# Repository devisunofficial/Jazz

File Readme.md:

# Jazz

Jazz is a bluetooth speaker that uses ESP32 for bluetooth connection

It focuses on minimalism and uses Audiophile grade equipments for good soundquality

### Features:

 - Compact design 
 - Capacitive Sensor to enter pairing mode
 - Toggle switch to On-Off speaker.
 - Daytone Speaker and Passive Radiator

### CAD Model:
It has 3 separate printed pieces. The Enclousure, the Speaker Holder to support driver and passive radiator, and Top mesh to cover driver.
Made in Autodesk Fusion.

### PCB:
Here's my PCB! It was made in KiCad. 

Schematic : 
PCB Footprint : 

### Firmware Overview:
Currently Firmware is underdevelopment so there is some time to finished product.
This speaker uses C++ firmware and Arduino IDE for Flashing.

### Assembly Instructions :
1. Flash Firmware in XIAO ESO32
2. Solder Pairing Switch, Kill Switch, Speaker, Battery
3. Test everything works
4. Apply Epoxy layer(not neccessary though but better if we do) inside shell to prevent air from leaking
5. Glue togetther the Speaker and Passive Radiater to Speaker holder (to prevent air from leaking) along with screws
6. Screw Speaker holder and Top Mesh to Encloudure.

### BOM Table
|Name|Use|Quantity|Distributer|
|-----|---|-------|-----------|
|Battery|Power Source|1|Robu|
|PCB|Main-Circuit|1|JLCPCB|
|Toggle switch|On-Off|1|Amazon|
|XIAO ESP32|Bluetooth SoC|1|Amazon|
|Speaker|Main Driver|1|Parts Express|
|Capacitive Touch Button|Pairing Mode|1|Amazon|
|AirTight Glue|Prevent Air Leaking|1|Amazon|

### Extra Stuff
I have provided an extra 3D printing Part in PR folder in CAD Folder because rather then paying $88 in shipping.
I didn't made that, and I don't have refinement in skills to make that. 
#### **CREDITS**  https://www.thingiverse.com/zx82net

Also I have added all screenshots of Cart in Screenshots_Cart Folder

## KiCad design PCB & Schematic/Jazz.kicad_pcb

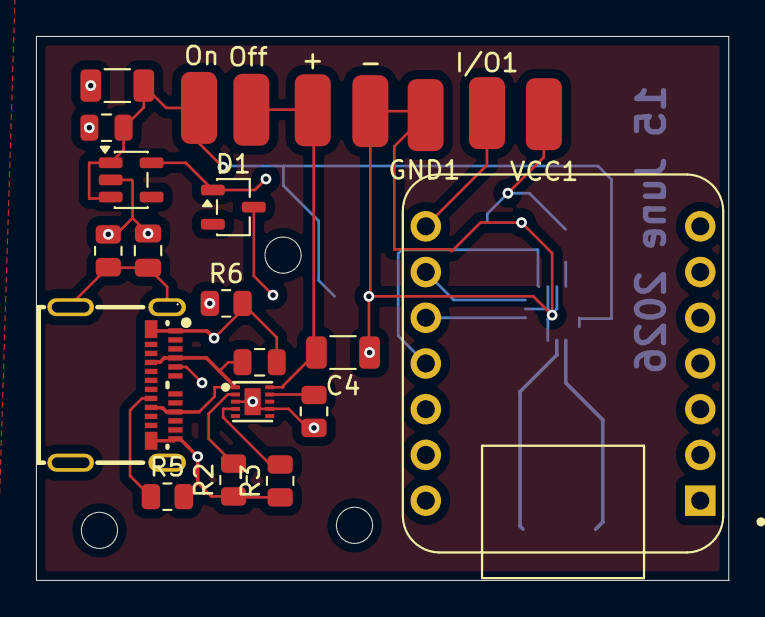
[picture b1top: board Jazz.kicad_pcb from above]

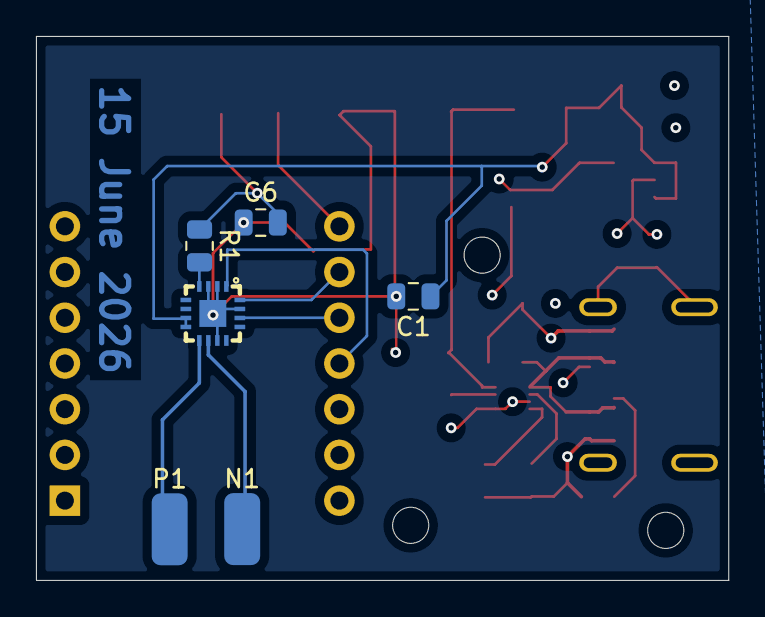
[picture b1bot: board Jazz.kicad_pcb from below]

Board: 4 copper layers, 38.5 x 30.2 mm, 29 parts (6 on the bottom side), 19 nets.

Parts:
+: MountingHole_Pad; SolderWirePad_1x01_SMD_2x4mm
-: MountingHole_Pad; SolderWirePad_1x01_SMD_2x4mm
C1: 0.1; C_0805_2012Metric
C2: 10; C_1206_3216Metric
C3, C5, C6: 1; C_0805_2012Metric
C4: 4.7; C_1206_3216Metric
C7: 4.7n; C_0805_2012Metric
D1: BAT54_C8590; SOT-23-3
GND1: MountingHole_Pad; SolderWirePad_1x01_SMD_2x4mm
I/O1: MountingHole_Pad; SolderWirePad_1x01_SMD_2x4mm
N1: MountingHole_Pad; SolderWirePad_1x01_SMD_2x4mm
Off: MountingHole_Pad; SolderWirePad_1x01_SMD_2x4mm
On: MountingHole_Pad; SolderWirePad_1x01_SMD_2x4mm
P1: MountingHole_Pad; SolderWirePad_1x01_SMD_2x4mm
R1: 560k; R_0805_2012Metric
R2: 1.1k; R_0805_2012Metric
R3: 2k; R_0805_2012Metric
R4: 10k; R_0805_2012Metric
R5, R6: 5.1k; R_0805_2012Metric
R7: 1M; R_0805_2012Metric
U1: XIAO-nRF52840-DIP; XIAO-Generic-Thruhole-14P-2.54-21X17.8MM
U2: TLV75533PDBVR; SOT-23-5
U3: BQ24040DSQT; WSON-10_L2.0-W2.0-P0.40-TL-EP
U4: MAX98357AETE+T; TQFN-16_L3.0-W3.0-P0.50-BL-EP1.5
USB-C-Port1: 105450-0101; USB-C-SMD_TYPE-C-USB-18
VCC1: MountingHole_Pad; SolderWirePad_1x01_SMD_2x4mm

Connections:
3.3V: C6.2, D1.1 (A), R1.1, U2.5 (OUT), VCC1.1
BCLK: U1.9 (P1.13_D8_SCK), U4.16 (BCLK)
Battery-Rail Out: +.1, C4.2, Off.1, U3.10 (OUT)
DIN: U1.11 (P1.15_D10_MOSI), U4.1 (DIN)
Diode Out: D1.3 (K), U1.12 (3V3)
GND: -.1, C1.2, C2.2, C3.1, C4.1, C5.1, C6.1, C7.1, GND1.1, R2.1, R3.1, R4.1, R5.2, R6.2, R7.1, U1.13 (GND), U2.2 (GND), U3.3 (VSS), U3.7 (ISET2), U3.11 (EP), U4.2 (GAIN_SLOT), U4.3 (GND), U4.11 (GND), U4.15 (GND), U4.17 (EP), USB-C-Port1.A1 (GND), USB-C-Port1.A12 (GND), USB-C-Port1.B1 (GND), USB-C-Port1.B12 (GND)
GROUND: C7.2, R7.2, USB-C-Port1.0
LRCK: U1.10 (P1.14_D9_MISO), U4.14 (LRCLK)
unnamed: R2.2, U3.2 (ISET)
unnamed: R3.2, U3.4 (PRETERM)
unnamed: R4.2, U3.9 (TS)
unnamed: R1.2, U4.4 (~SD_MODE)
unnamed: R6.1, USB-C-Port1.A5 (CC1)
unnamed: R5.1, USB-C-Port1.B5 (CC2)
OUT-N: N1.1, U4.10 (OUTN)
OUT-P: P1.1, U4.9 (OUTP)
Pairing-Mode: I/O1.1, U1.8 (P1.12_D7_RX)
Switch_OUT: C1.1, C2.1, C5.2, On.1, U2.1 (IN), U2.3 (EN), U4.7 (VDD), U4.8 (VDD)
VBUS: C3.2, U3.1 (IN), USB-C-Port1.A4 (VBUS), USB-C-Port1.A9 (VBUS), USB-C-Port1.B4 (VBUS), USB-C-Port1.B9 (VBUS)

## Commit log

2026-06-16 Readme-Partial
2026-06-16 Readme Done
    Updated the Readme.md to include additional details about the BOM table and corrected formatting issues.
2026-06-16 Bom & Readme
2026-06-16 Readme
2026-06-16 I guess, it's Done
2026-06-28 Update Readme with assembly instructions and formatting
    Added assembly instructions and fixed formatting issues.
2026-06-28 Possibly Done
2026-06-28 Credits Given
